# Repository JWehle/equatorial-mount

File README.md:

# equatorial-mount
Driver board for an dual stepper motors in an equatorial mount for astrophotography.

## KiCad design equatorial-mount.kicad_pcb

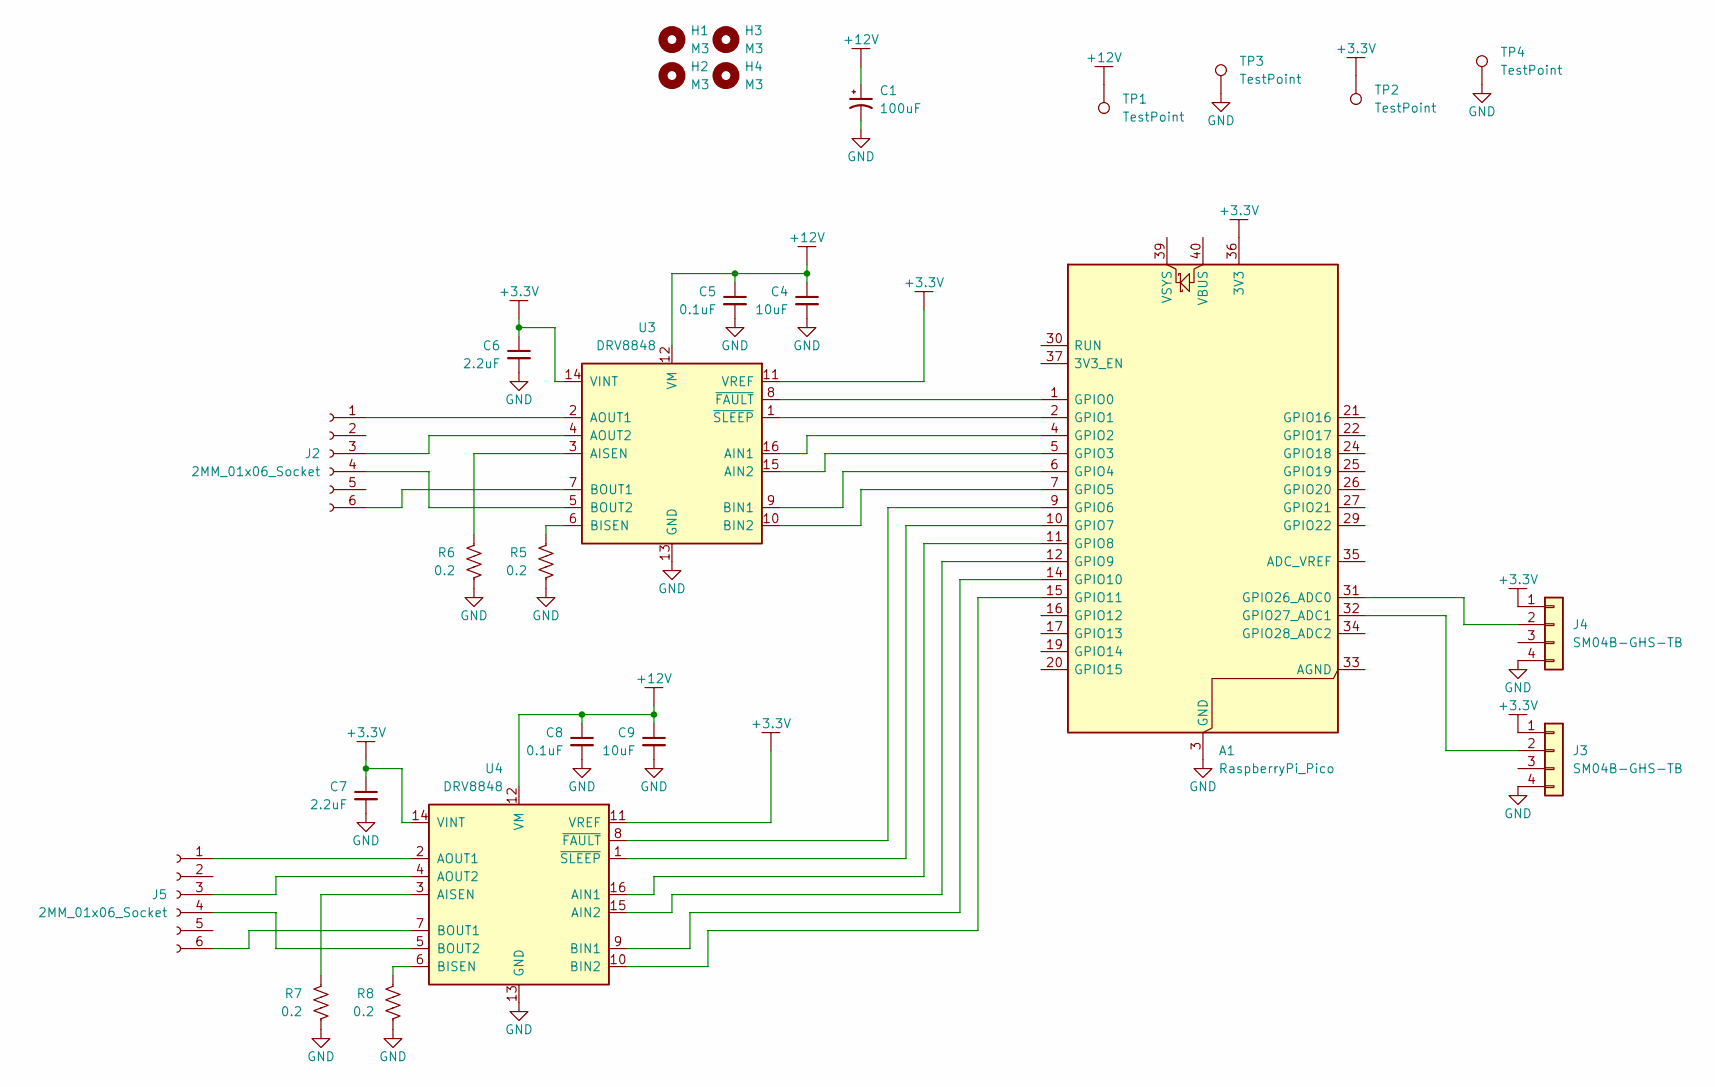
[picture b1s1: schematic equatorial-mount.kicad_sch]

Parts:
A1: RaspberryPi_Pico; RaspberryPi_Pico_Common_Unspecified
C1: 100uF; CP_Elec_10x7.7
C4, C9: 10uF; C_1206_3216Metric
C5, C8: 0.1uF; C_0603_1608Metric
C6, C7: 2.2uF; C_0603_1608Metric
H1, H2, H3, H4: M3; MountingHole_3.2mm_M3
J2, J5: 2MM_01x06_Socket; PinSocket_1x06_P2.00mm_Vertical
J3, J4: SM04B-GHS-TB; JST_GH_SM04B-GHS-TB_1x04-1MP_P1.25mm_Horizontal
R5, R6, R7, R8: 0.2; R_1206_3216Metric
TP1, TP2, TP3, TP4: TestPoint; TestPoint_Keystone_5016_Vias
U3, U4: DRV8848; TSSOP-16-1EP_4.4x5mm_P0.65mm

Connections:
+3.3V: A1.36 (3V3), C6.1, C7.1, J3.1, J4.1, TP2.1, U3.11 (VREF), U3.14 (VINT), U4.11 (VREF), U4.14 (VINT)
+12V: C1.1, C4.1, C5.1, C8.1, C9.1, TP1.1, U3.12 (VM), U4.12 (VM)
GND: A1.3 (GND), A1.8 (GND), A1.13 (GND), A1.18 (GND), A1.23 (GND), A1.28 (GND), A1.38 (GND), C1.2, C4.2, C5.2, C6.2, C7.2, C8.2, C9.2, J3.4, J4.4, R5.2, R6.2, R7.2, R8.2, TP3.1, TP4.1, U3.13 (GND), U3.17 (GND), U4.13 (GND), U4.17 (GND)
unnamed: A1.1 (GPIO0), U3.8 (~FAULT)
unnamed: A1.2 (GPIO1), U3.1 (~SLEEP)
unnamed: A1.4 (GPIO2), U3.16 (AIN1)
unnamed: A1.5 (GPIO3), U3.15 (AIN2)
unnamed: A1.6 (GPIO4), U3.9 (BIN1)
unnamed: A1.7 (GPIO5), U3.10 (BIN2)
unnamed: A1.9 (GPIO6), U4.8 (~FAULT)
unnamed: A1.10 (GPIO7), U4.1 (~SLEEP)
unnamed: A1.11 (GPIO8), U4.16 (AIN1)
unnamed: A1.12 (GPIO9), U4.15 (AIN2)
unnamed: A1.14 (GPIO10), U4.9 (BIN1)
unnamed: A1.15 (GPIO11), U4.10 (BIN2)
unnamed: A1.31 (GPIO26_ADC0), J4.2
unnamed: A1.32 (GPIO27_ADC1), J3.2
unnamed: J2.1, U3.2 (AOUT1)
unnamed: J2.3, U3.4 (AOUT2)
unnamed: J2.4, U3.5 (BOUT2)
unnamed: J2.6, U3.7 (BOUT1)
unnamed: J5.1, U4.2 (AOUT1)
unnamed: J5.3, U4.4 (AOUT2)
unnamed: J5.4, U4.5 (BOUT2)
unnamed: J5.6, U4.7 (BOUT1)
unnamed: R6.1, U3.3 (AISEN)
unnamed: R5.1, U3.6 (BISEN)
unnamed: R7.1, U4.3 (AISEN)
unnamed: R8.1, U4.6 (BISEN)

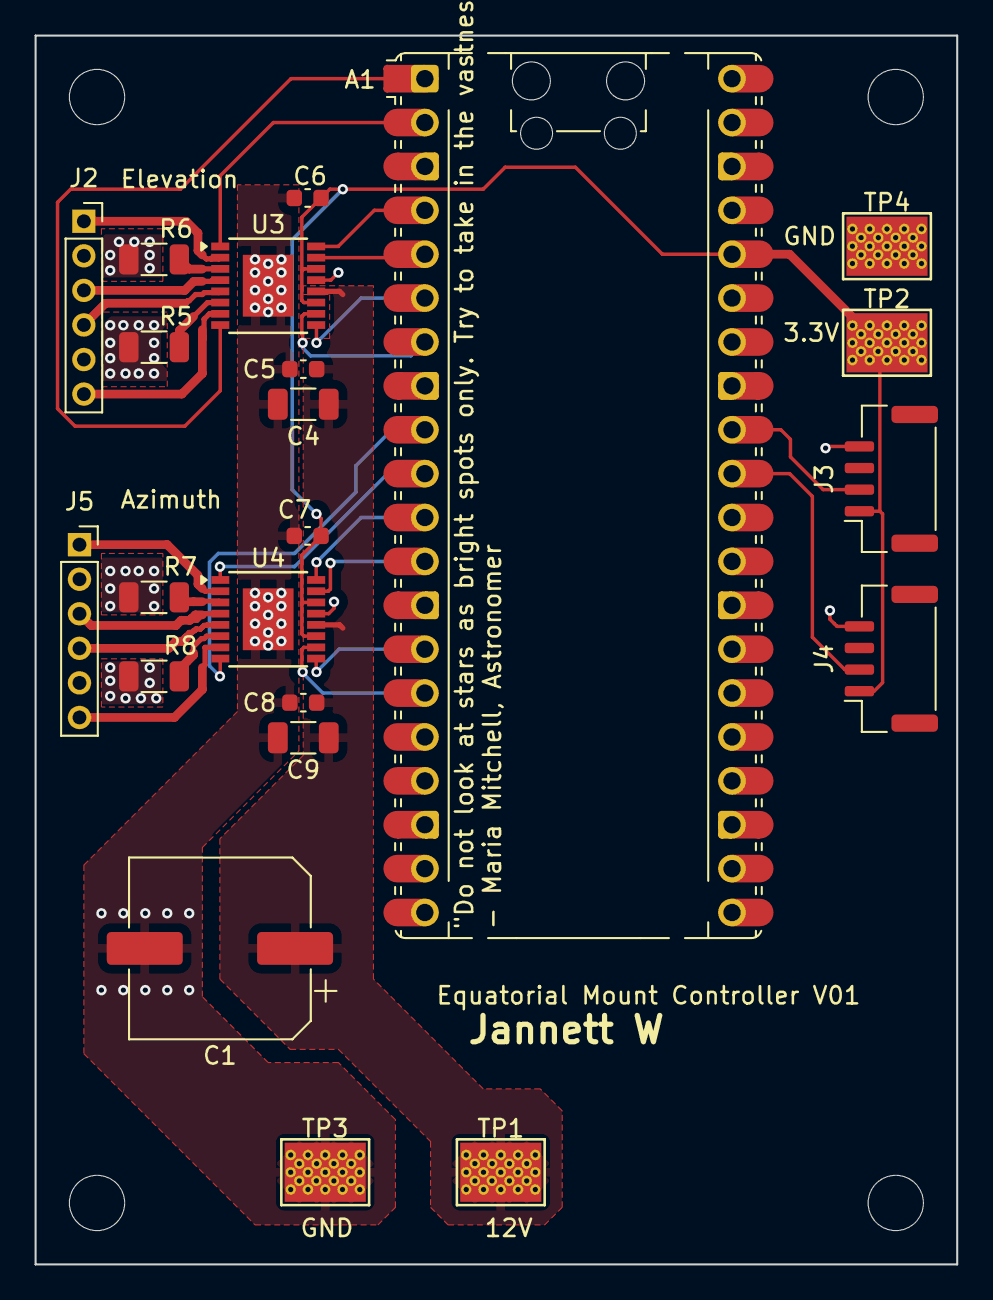
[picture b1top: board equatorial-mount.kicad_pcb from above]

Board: 2 copper layers, 53.3 x 71.1 mm, 26 parts (0 on the bottom side), 29 nets.

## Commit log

2025-03-05 working on schematic
2025-06-14 layout
2025-06-15 finished and gerbers
